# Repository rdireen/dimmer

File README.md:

Dimmer circuit and code
=======================

Making a circuit that can be connected to serially for control. I'm making this to control a few edison lights via homeassistant.

5/20/2018

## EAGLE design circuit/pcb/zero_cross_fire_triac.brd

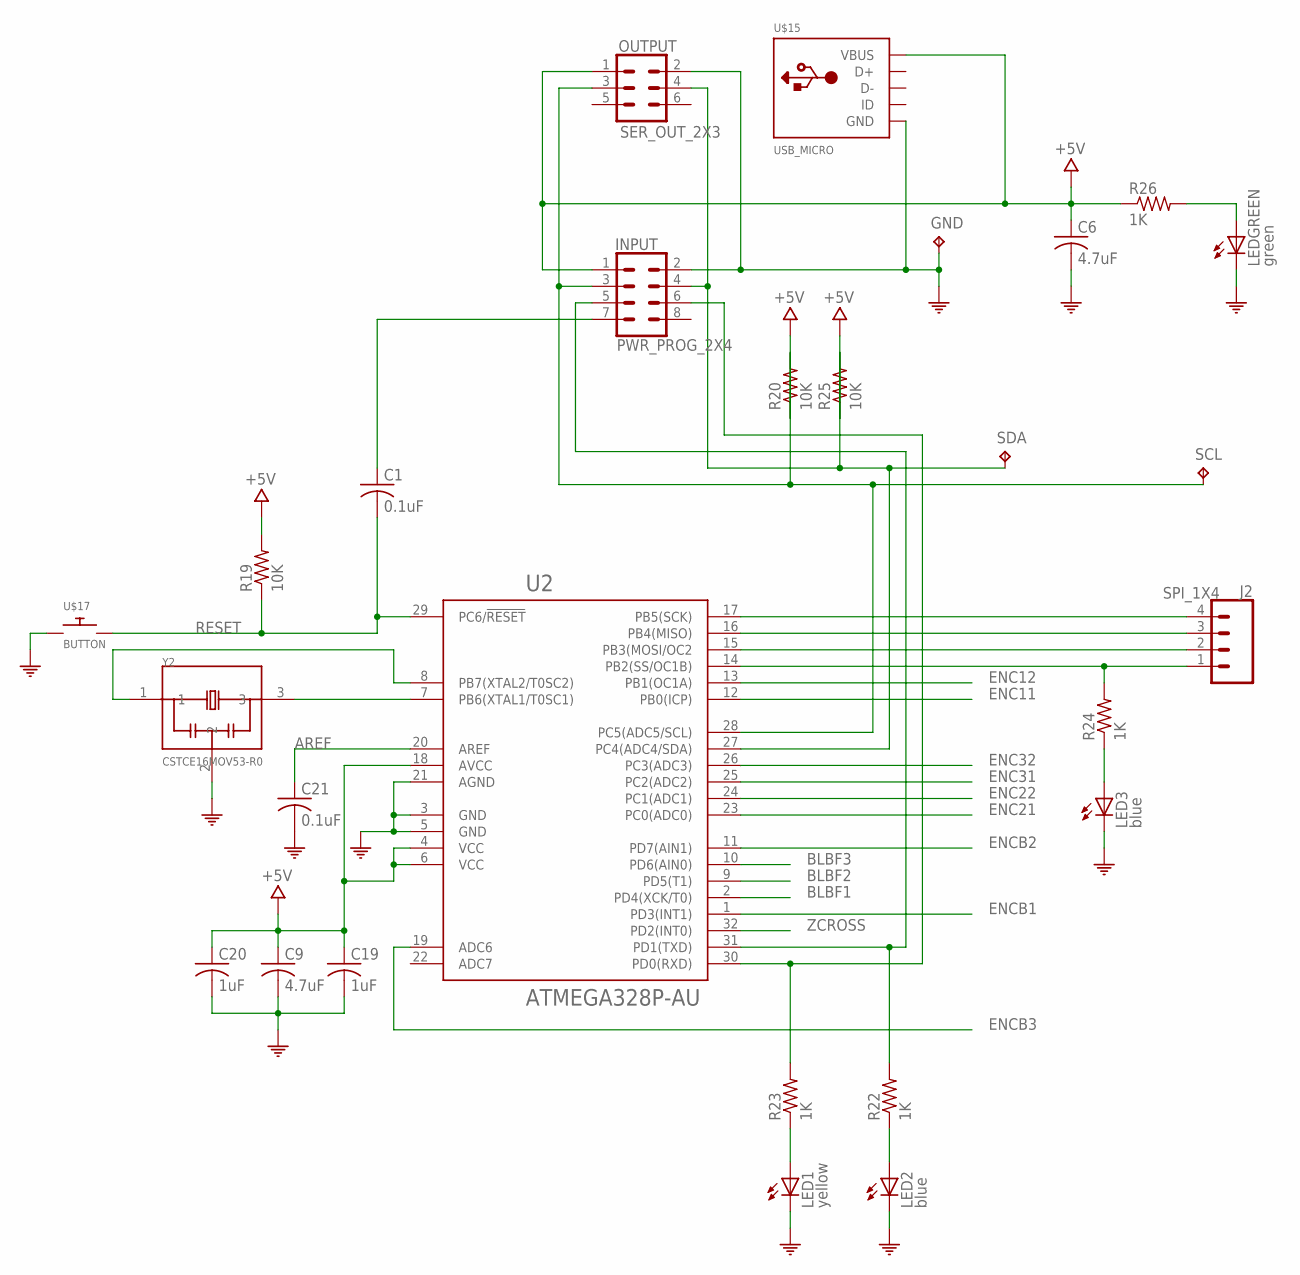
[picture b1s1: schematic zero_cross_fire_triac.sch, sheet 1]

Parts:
C1, C21: 0.1uF; C0805
C6, C9: 4.7uF; C0805
C19, C20: 1uF; C0805
GND: TEST_POINT; TEST
INPUT: PWR_PROG_2X4; 2X04
J2: SPI_1X4; 1X04-BIG
LED1: yellow; LED1
LED2, LED3: blue; LED1
LEDGREEN: green; LED1
OUTPUT: SER_OUT_2X3; 2X03
R19, R20, R25: 10K; R0805
R22, R23, R24, R26: 1K; R0805
SCL: TEST_POINT; TEST
SDA: TEST_POINT; TEST
U2: ATMEGA328P-AU; QFP80P900X900X120-32N
U$15: USB_MICRO; USB-MICRO-SMD-CUSTOM
U$17: BUTTON; PUSHBUTTON
Y2: CSTCE16MOV53-R0; OSC_CSTCE8M00G55-R0

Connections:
+5V: C6.1, C9.1, C19.1, C20.1, INPUT.1, OUTPUT.1, R19.2, R20.1, R25.1, R26.1, U2.4 (VCC), U2.6 (VCC), U2.18 (AVCC), U$15.VBUS; also elsewhere on the board
AREF: C21.1, U2.20 (AREF)
BLBF1: U2.2 (PD4(XCK/T0)); also elsewhere on the board
BLBF2: U2.9 (PD5(T1)); also elsewhere on the board
BLBF3: U2.10 (PD6(AIN0)); also elsewhere on the board
COM: C6.2, C9.2, C19.2, C20.2, C21.2, GND.1, INPUT.2, LED1.1 (C), LED2.1 (C), LED3.1 (C), LEDGREEN.1 (C), OUTPUT.2, U2.3 (GND), U2.5 (GND), U2.21 (AGND), U$15.GND, U$15.SHIELD1 (GND), U$15.SHIELD2 (GND), U$15.SHIELD3 (GND), U$17.1, U$17.2, Y2.2; also elsewhere on the board
D0/RX: INPUT.6, R23.2, U2.30 (PD0(RXD))
D1/TX: INPUT.5, R22.2, U2.31 (PD1(TXD))
ENC11: U2.12 (PB0(ICP)); also elsewhere on the board
ENC12: U2.13 (PB1(OC1A)); also elsewhere on the board
ENC21: U2.23 (PC0(ADC0)); also elsewhere on the board
ENC22: U2.24 (PC1(ADC1)); also elsewhere on the board
ENC31: U2.25 (PC2(ADC2)); also elsewhere on the board
ENC32: U2.26 (PC3(ADC3)); also elsewhere on the board
ENCB1: U2.1 (PD3(INT1)); also elsewhere on the board
ENCB2: U2.11 (PD7(AIN1)); also elsewhere on the board
ENCB3: U2.19 (ADC6); also elsewhere on the board
unnamed: U2.8 (PB7(XTAL2/T0SC2)), Y2.1
unnamed: J2.1, R24.2, U2.14 (PB2(SS/OC1B))
unnamed: LEDGREEN.2 (A), R26.2
unnamed: U2.7 (PB6(XTAL1/T0SC1)), Y2.3
unnamed: J2.2, U2.15 (PB3(MOSI/OC2)
unnamed: C1.1, INPUT.7
unnamed: LED2.2 (A), R22.1
unnamed: J2.3, U2.16 (PB4(MISO))
unnamed: J2.4, U2.17 (PB5(SCK))
unnamed: LED1.2 (A), R23.1
unnamed: LED3.2 (A), R24.1
RESET: C1.2, R19.1, U2.29 (PC6/!RESET), U$17.3, U$17.4
SCL: INPUT.3, OUTPUT.3, R20.2, SCL.1, U2.28 (PC5(ADC5/SCL))
SDA: INPUT.4, OUTPUT.4, R25.2, SDA.1, U2.27 (PC4(ADC4/SDA))
ZCROSS: U2.32 (PD2(INT0)); also elsewhere on the board

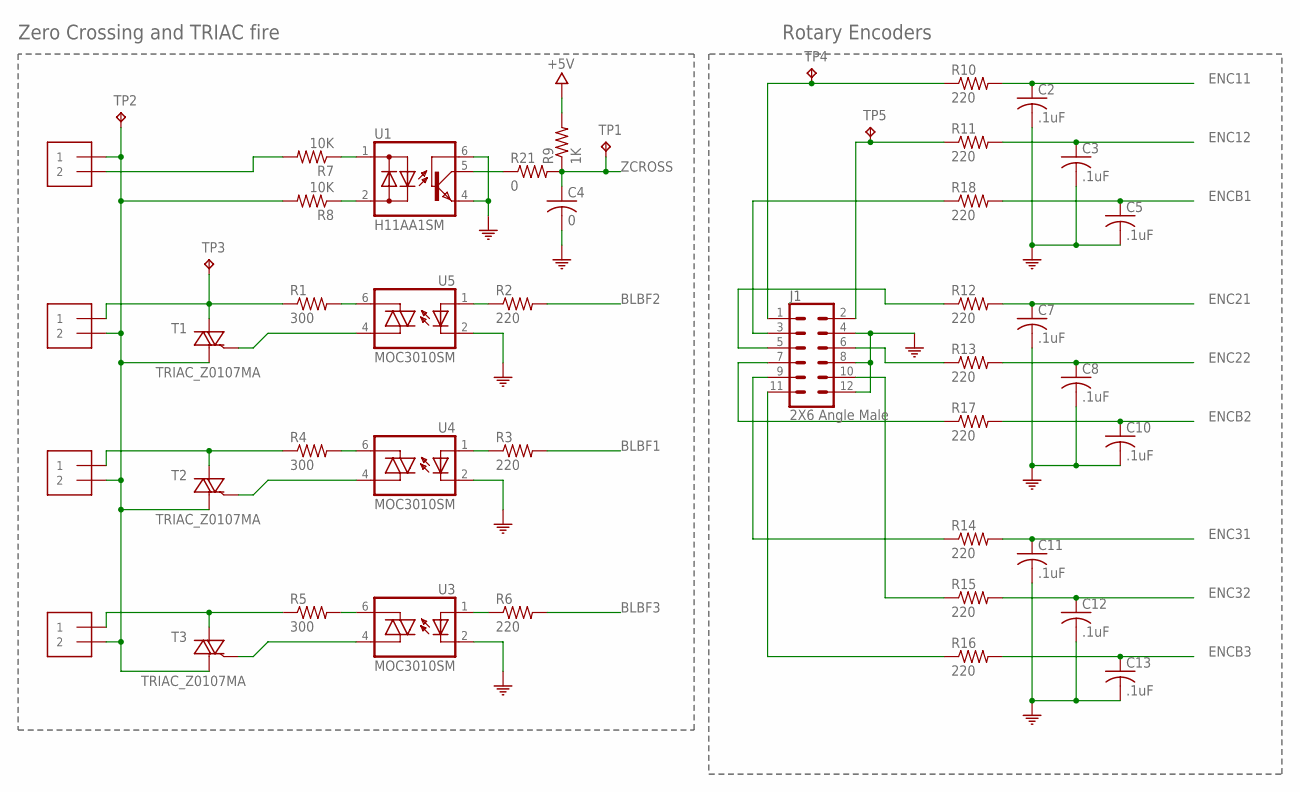
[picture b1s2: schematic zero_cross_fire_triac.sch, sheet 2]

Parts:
BLB1, BLB2, BLB3: SCREW_BLOCK_2PIN; 1X2-200MIL
C2, C3, C5, C7, C8, C10, C11, C12, C13: .1uF; C0805
C4: 0; C0805
J1: 2X6 Angle Male; 2X06
MAIN: SCREW_BLOCK_2PIN; 1X2-200MIL
R1, R4, R5: 300; R1210
R2, R3, R6, R10, R11, R12, R13, R14, R15, R16, R17, R18: 220; R0805
R7, R8: 10K; RLTR50
R9: 1K; R0805
R21: 0; R0805
T1, T2, T3: TRIAC_Z0107MA; TO92
TP1, TP2, TP3, TP4, TP5: TEST_POINT; TEST
U1: H11AA1SM; DIL6-SMD
U3, U4, U5: MOC3010SM; DIL6-SMD

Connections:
+5V: R9.2; also elsewhere on the board
BLBF1: R3.2; also elsewhere on the board
BLBF2: R2.2; also elsewhere on the board
BLBF3: R6.2; also elsewhere on the board
COM: C2.2, C3.2, C4.2, C5.2, C7.2, C8.2, C10.2, C11.2, C12.2, C13.2, J1.4, J1.8, J1.12, U1.4 (E), U1.6 (B), U3.2 (C), U4.2 (C), U5.2 (C); also elsewhere on the board
ENC11: C2.1, R10.2; also elsewhere on the board
ENC12: C3.1, R11.2; also elsewhere on the board
ENC21: C7.1, R12.2; also elsewhere on the board
ENC22: C8.1, R13.2; also elsewhere on the board
ENC31: C11.1, R14.2; also elsewhere on the board
ENC32: C12.1, R15.2; also elsewhere on the board
ENCB1: C5.1, R18.2; also elsewhere on the board
ENCB2: C10.1, R17.2; also elsewhere on the board
ENCB3: C13.1, R16.2; also elsewhere on the board
MAINNUETRAL: BLB1.1 (2), BLB2.1 (2), BLB3.1 (2), MAIN.2 (1), R8.P$2 (2), T1.1 (A1), T2.1 (A1), T3.1 (A1), TP2.1
unnamed: BLB3.2 (1), R5.1, T3.3 (A2)
unnamed: R5.2, U3.6 (A2)
unnamed: R6.1, U3.1 (A)
unnamed: BLB1.2 (1), R4.1, T2.3 (A2)
unnamed: R4.2, U4.6 (A2)
unnamed: R3.1, U4.1 (A)
unnamed: BLB2.2 (1), R1.1, T1.3 (A2), TP3.1
unnamed: R2.1, U5.1 (A)
unnamed: R8.P$1 (1), U1.2 (AC2)
unnamed: J1.1, R10.1, TP4.1
unnamed: MAIN.1 (2), R7.P$2 (2)
unnamed: R7.P$1 (1), U1.1 (AC1)
unnamed: R1.2, U5.6 (A2)
unnamed: T1.2 (G), U5.4 (A1)
unnamed: T2.2 (G), U4.4 (A1)
unnamed: T3.2 (G), U3.4 (A1)
unnamed: R21.1, U1.5 (C)
unnamed: J1.3, R18.1
unnamed: J1.5, R12.1
unnamed: J1.7, R17.1
unnamed: J1.9, R14.1
unnamed: J1.11, R16.1
unnamed: J1.2, R11.1, TP5.1
unnamed: J1.6, R13.1
unnamed: J1.10, R15.1
ZCROSS: C4.1, R9.1, R21.2, TP1.1; also elsewhere on the board

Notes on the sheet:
Rotary Encoders
Zero Crossing and TRIAC fire

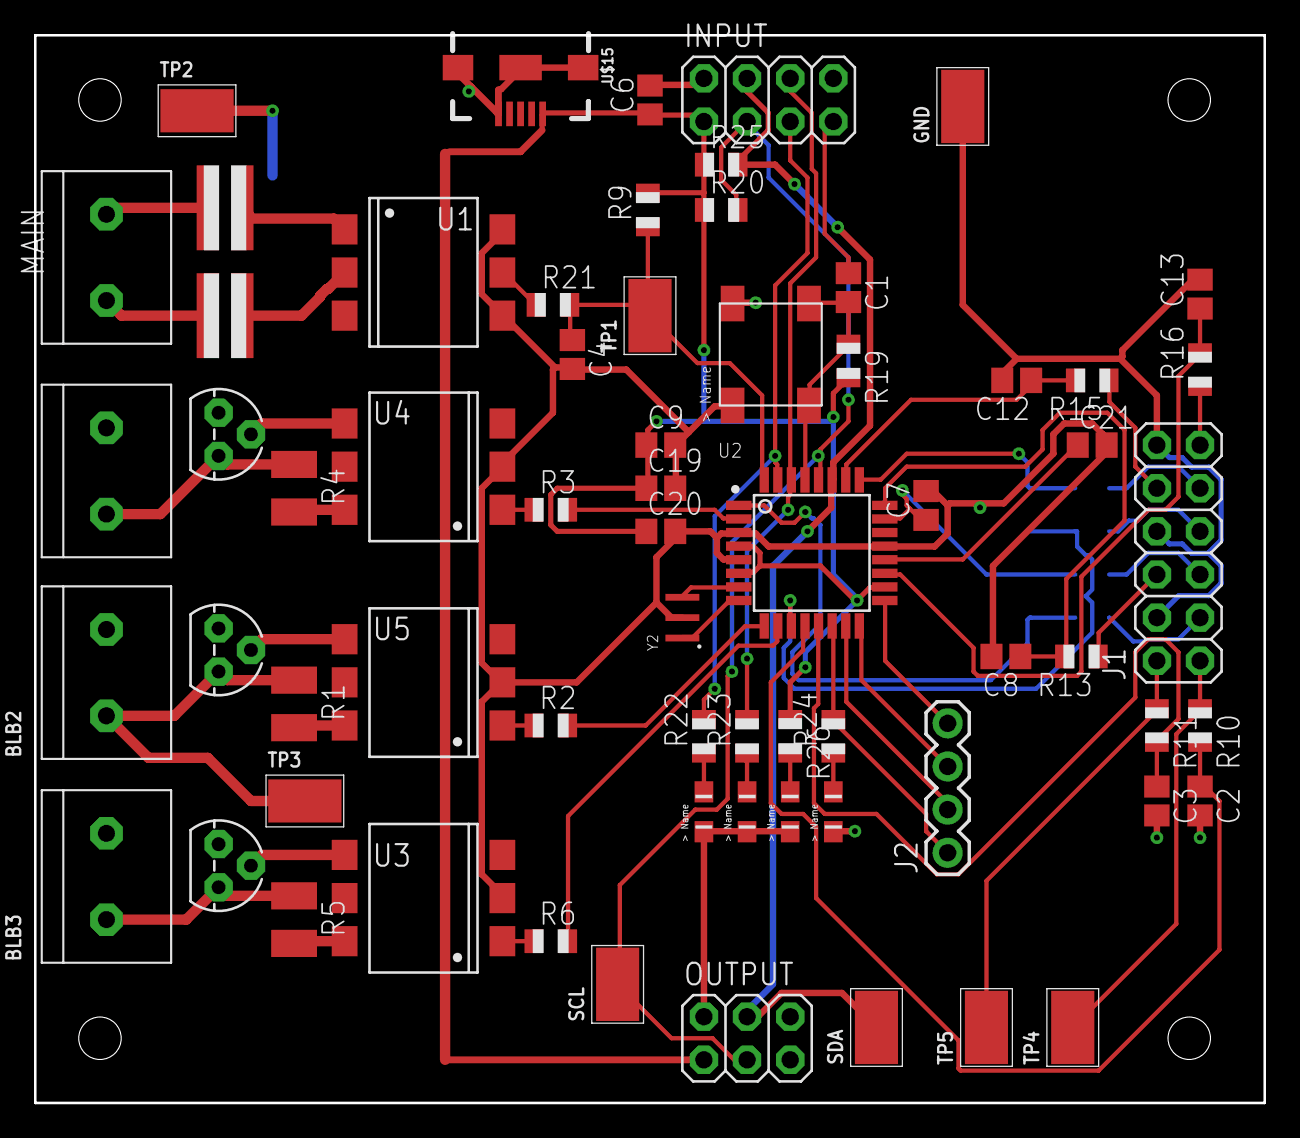
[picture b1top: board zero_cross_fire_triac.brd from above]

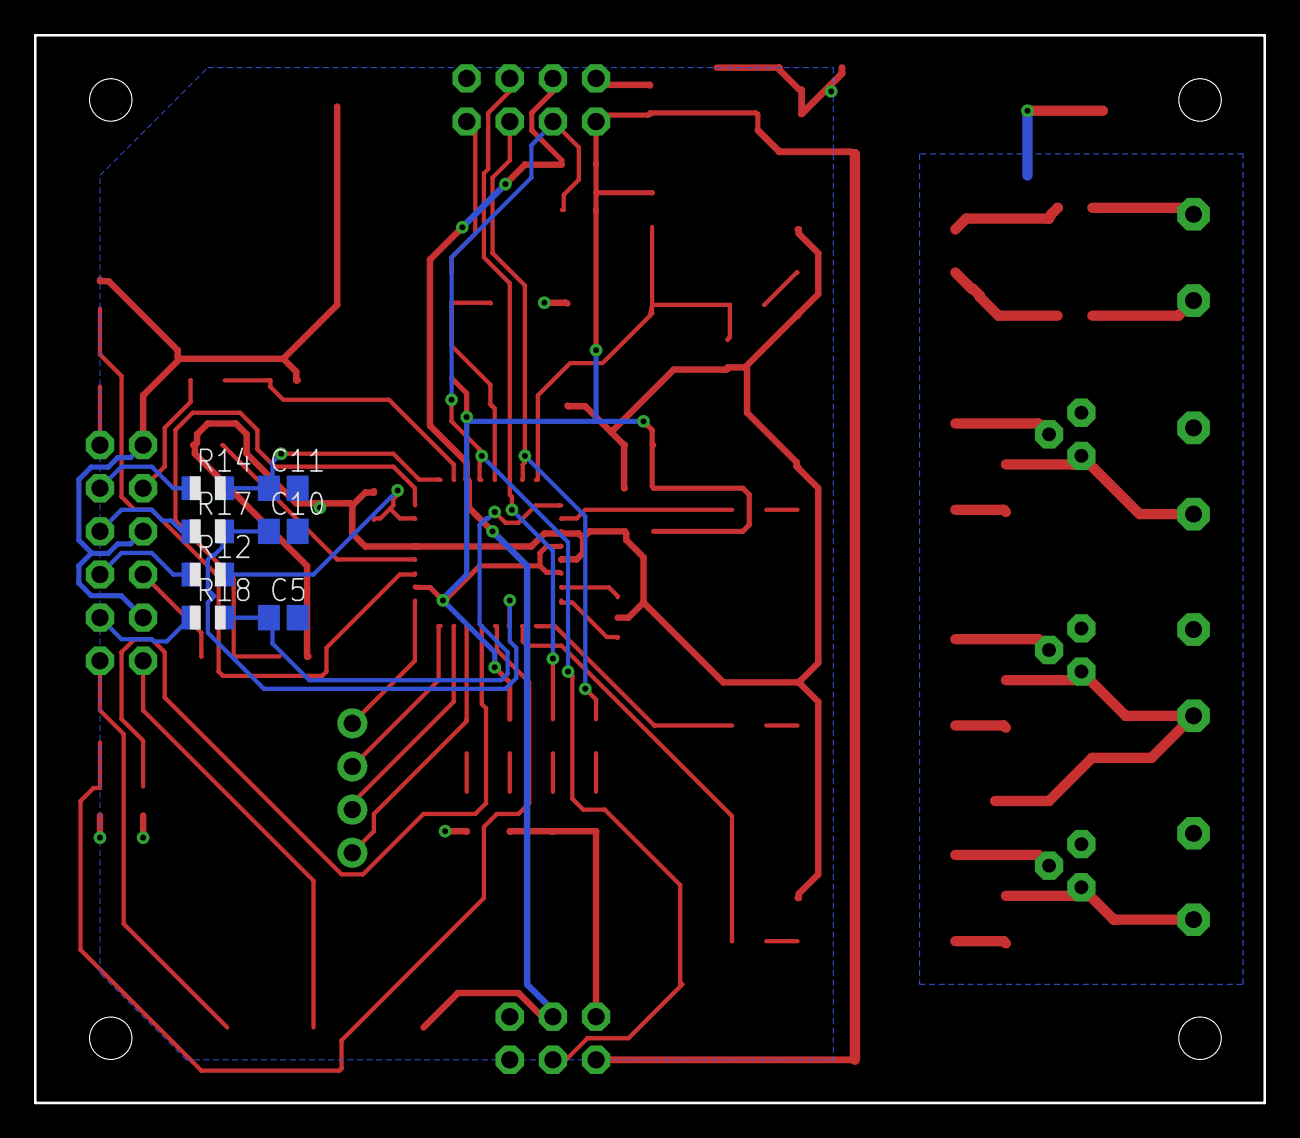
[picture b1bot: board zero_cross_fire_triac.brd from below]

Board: 2 copper layers, 72.4 x 62.9 mm, 73 parts (7 on the bottom side), 58 nets.

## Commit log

2018-05-20 Initial commit of the dimmer project
2018-05-20 ready to refactor
2018-05-20 reorganized files to work with arduino
2018-05-20 starting cleanup
